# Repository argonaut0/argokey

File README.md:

# Unnamed Keyboard Project

A Custom 65% Mechanical Keyboard with RGB lighting, an OLED status screen, and volume knob.

Possibly with the first ever keyboard firmware fulling supporting multithreading?

### References

- https://datasheets.raspberrypi.com/rp2040/rp2040-datasheet.pdf
- https://datasheets.raspberrypi.com/rp2040/hardware-design-with-rp2040.pdf

### Symbols and Models
- https://github.com/daprice/keyswitches.pretty
- https://app.ultralibrarian.com/details/718f6c74-6ffb-11eb-9033-0a34d6323d74/Raspberry-Pi/RP2040
- https://app.ultralibrarian.com/details/76A34700-1D87-11E9-AB3A-0A3560A4CCCC/Winbond/W25Q64JVSSIQ

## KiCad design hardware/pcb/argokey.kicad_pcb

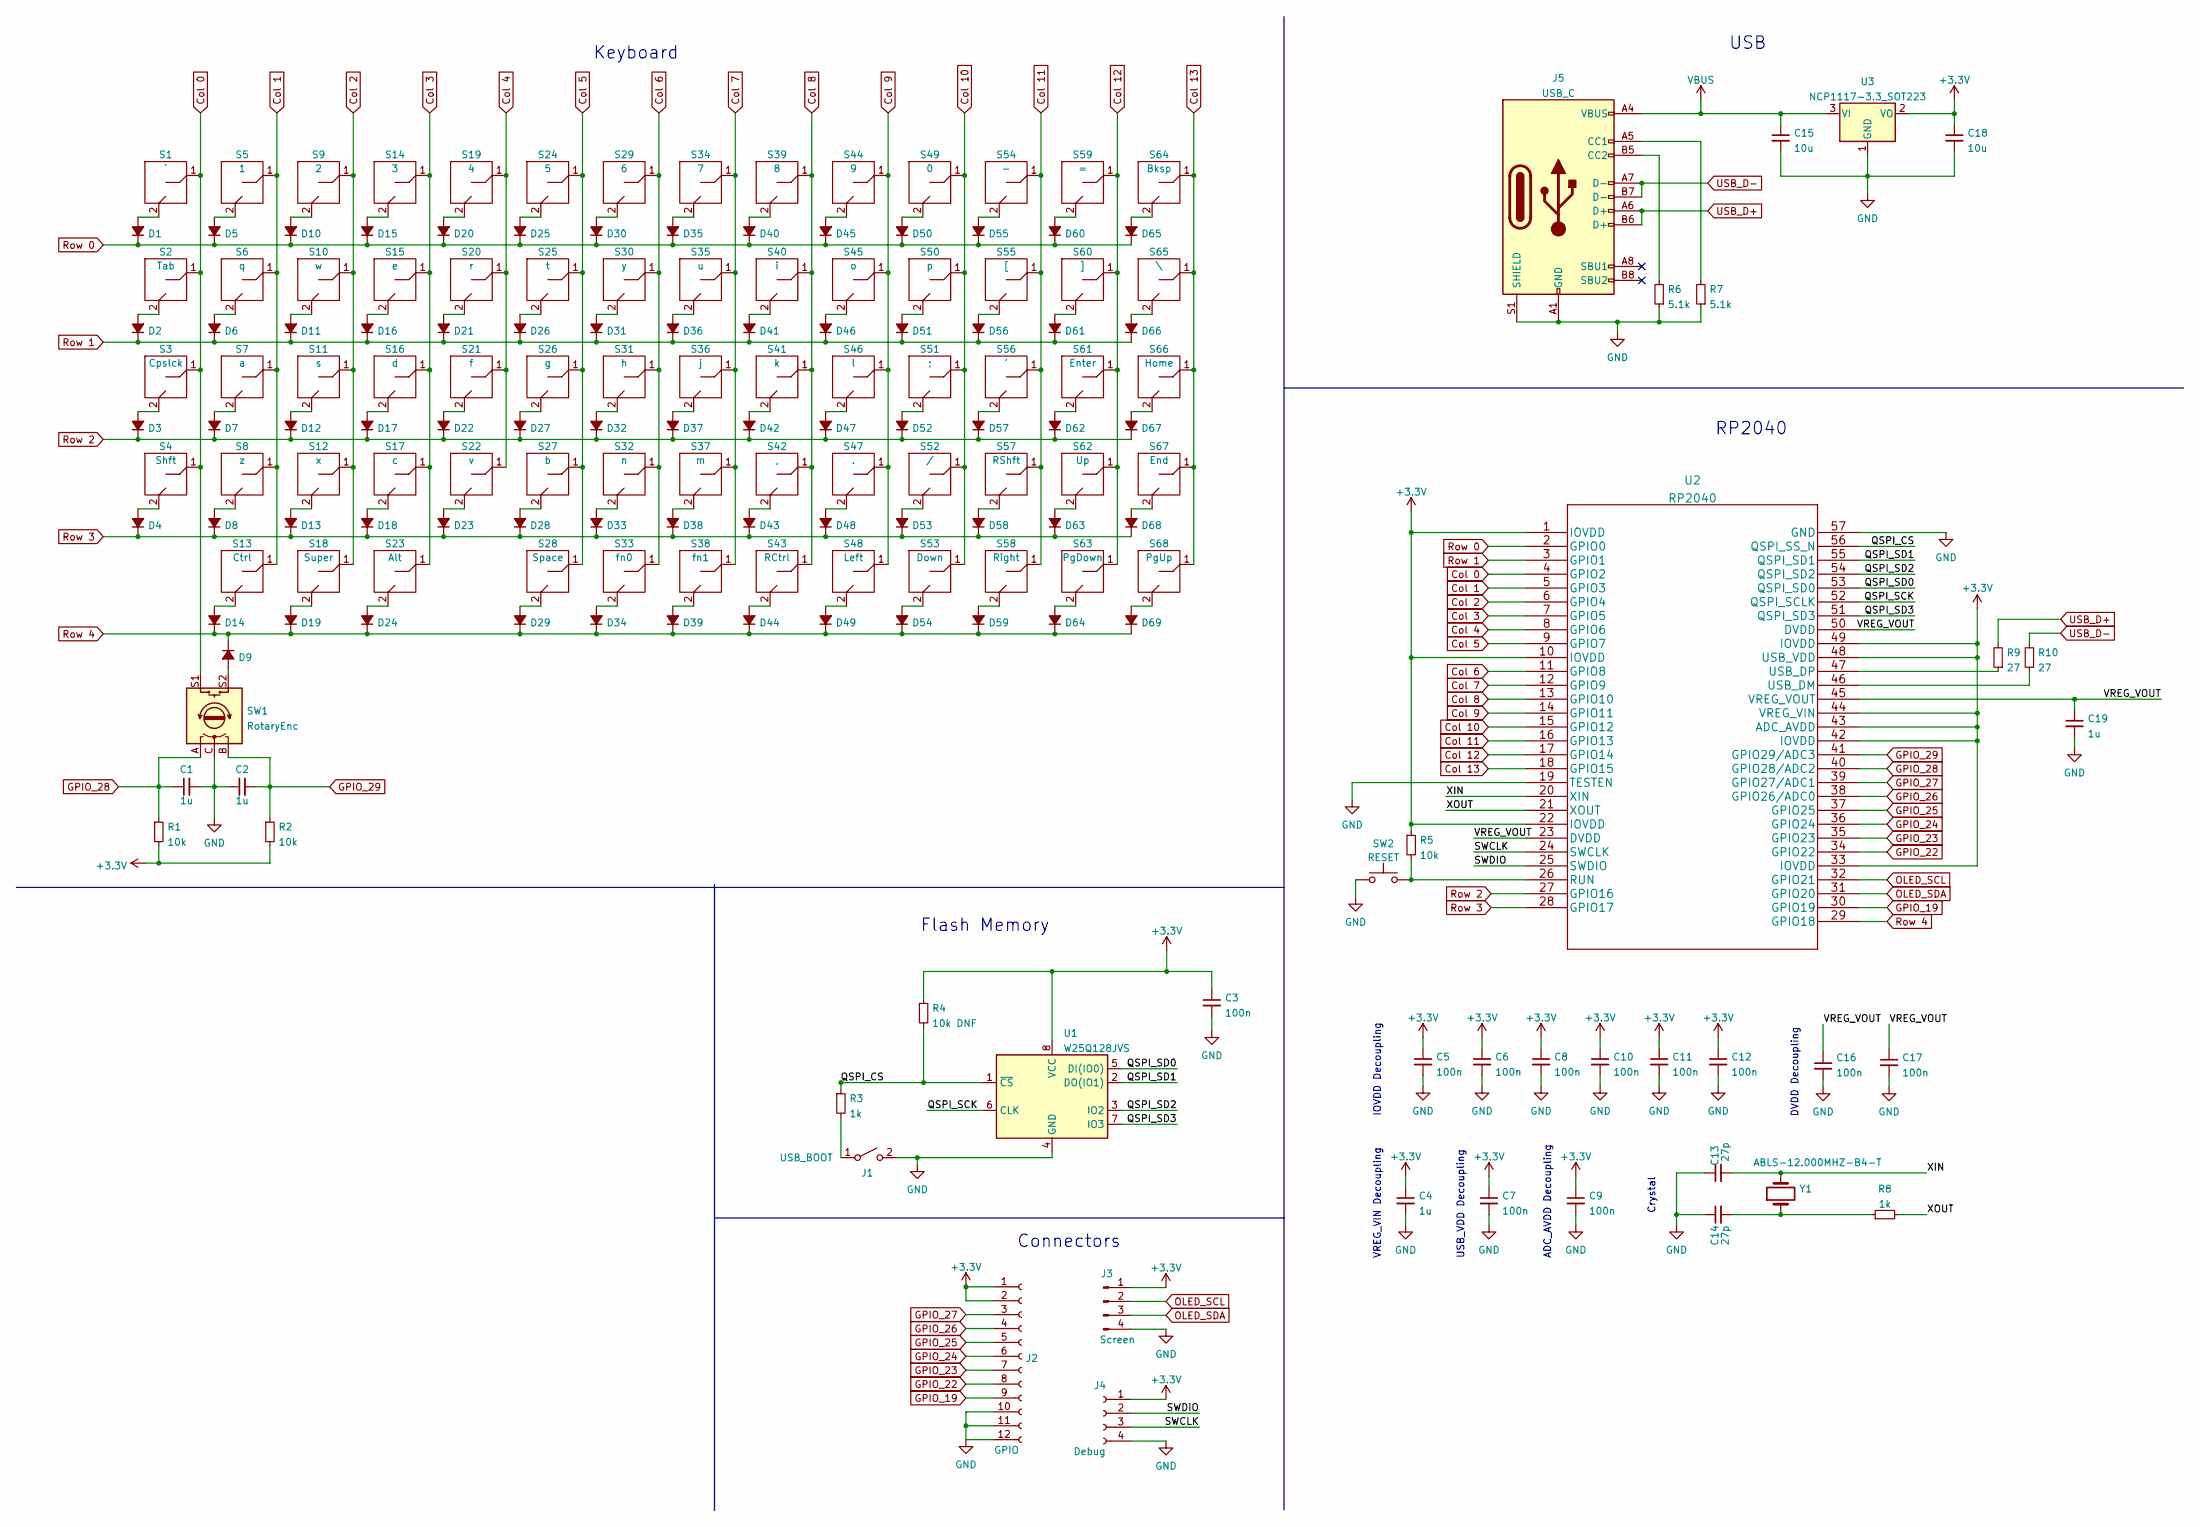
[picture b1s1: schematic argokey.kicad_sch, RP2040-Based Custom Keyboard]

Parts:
C1, C2, C4, C19: 1u; C_0402_1005Metric_Pad0.74x0.62mm_HandSolder
C3, C5, C6, C7, C8, C9, C10, C11, C12, C16, C17: 100n; C_0402_1005Metric_Pad0.74x0.62mm_HandSolder
C13, C14: 27p; C_0402_1005Metric_Pad0.74x0.62mm_HandSolder
C15, C18: 10u; C_0805_2012Metric_Pad1.18x1.45mm_HandSolder
D1, D2, D3, D4, D5, D6, D7, D8, D9, D10, D11, D12, D13, D14, D15, D16, D18, D19, D20, D21, D22, D23, D24, D25, D26, D27, D28, D29, D30, D31, D32, D33, D34, D35, D36, D37, D38, D39, D40, D41, D42, D43, D44, D45, D46, D47, D48, D49, D50, D51, D52, D53, D54, D55, D56, D57, D58, D59, D60, D61, D62, D63, D64, D65, D66, D67, D68, D69: D_SOD-123
D17: D_SOD-123
J1: USB_BOOT; SW_SPDT_PCM12
J2: GPIO; PinSocket_1x12_P2.54mm_Horizontal
J3: Screen; PinHeader_1x04_P2.54mm_Vertical
J4: Debug; PinSocket_1x04_P2.54mm_Horizontal
J5: USB_C; USB_C_Receptacle_GCT_USB4085
R1, R2, R5: 10k; R_0402_1005Metric_Pad0.72x0.64mm_HandSolder
R3, R8: 1k; R_0402_1005Metric_Pad0.72x0.64mm_HandSolder
R4: 10k DNF; R_0402_1005Metric_Pad0.72x0.64mm_HandSolder
R6, R7: 5.1k; R_0402_1005Metric_Pad0.72x0.64mm_HandSolder
R9, R10: 27; R_0402_1005Metric_Pad0.72x0.64mm_HandSolder
S1: `; SW_Cherry_MX_1.00u_PCB
S2: Tab; SW_Cherry_MX_1.50u_PCB
S3: Cpslck; SW_Cherry_MX_1.75u_PCB
S4: Shft; SW_Cherry_MX_2.25u_PCB
S5: 1; SW_Cherry_MX_1.00u_PCB
S6: q; SW_Cherry_MX_1.00u_PCB
S7: a; SW_Cherry_MX_1.00u_PCB
S8: z; SW_Cherry_MX_1.00u_PCB
S9: 2; SW_Cherry_MX_1.00u_PCB
S10: w; SW_Cherry_MX_1.00u_PCB
S11: s; SW_Cherry_MX_1.00u_PCB
S12: x; SW_Cherry_MX_1.00u_PCB
S13: Ctrl; SW_Cherry_MX_1.25u_PCB
S14: 3; SW_Cherry_MX_1.00u_PCB
S15: e; SW_Cherry_MX_1.00u_PCB
S16: d; SW_Cherry_MX_1.00u_PCB
S17: c; SW_Cherry_MX_1.00u_PCB
S18: Super; SW_Cherry_MX_1.25u_PCB
S19: 4; SW_Cherry_MX_1.00u_PCB
S20: r; SW_Cherry_MX_1.00u_PCB
S21: f; SW_Cherry_MX_1.00u_PCB
S22: v; SW_Cherry_MX_1.00u_PCB
S23: Alt; SW_Cherry_MX_1.25u_PCB
S24: 5; SW_Cherry_MX_1.00u_PCB
S25: t; SW_Cherry_MX_1.00u_PCB
S26: g; SW_Cherry_MX_1.00u_PCB
S27: b; SW_Cherry_MX_1.00u_PCB
S28: Space; SW_Cherry_MX_6.25u_PCB
S29: 6; SW_Cherry_MX_1.00u_PCB
S30: y; SW_Cherry_MX_1.00u_PCB
S31: h; SW_Cherry_MX_1.00u_PCB
S32: n; SW_Cherry_MX_1.00u_PCB
S33: fn0; SW_Cherry_MX_1.00u_PCB
S34: 7; SW_Cherry_MX_1.00u_PCB
S35: u; SW_Cherry_MX_1.00u_PCB
S36: j; SW_Cherry_MX_1.00u_PCB
S37: m; SW_Cherry_MX_1.00u_PCB
S38: fn1; SW_Cherry_MX_1.00u_PCB
S39: 8; SW_Cherry_MX_1.00u_PCB
S40: i; SW_Cherry_MX_1.00u_PCB
S41: k; SW_Cherry_MX_1.00u_PCB
S42: ,; SW_Cherry_MX_1.00u_PCB
S43: RCtrl; SW_Cherry_MX_1.00u_PCB
S44: 9; SW_Cherry_MX_1.00u_PCB
S45: o; SW_Cherry_MX_1.00u_PCB
S46: l; SW_Cherry_MX_1.00u_PCB
S47: .; SW_Cherry_MX_1.00u_PCB
S48: Left; SW_Cherry_MX_1.00u_PCB
S49: 0; SW_Cherry_MX_1.00u_PCB
S50: p; SW_Cherry_MX_1.00u_PCB
S51: ;; SW_Cherry_MX_1.00u_PCB
S52: /; SW_Cherry_MX_1.00u_PCB
S53: Down; SW_Cherry_MX_1.00u_PCB
S54: -; SW_Cherry_MX_1.00u_PCB
S55: [; SW_Cherry_MX_1.00u_PCB
S56: '; SW_Cherry_MX_1.00u_PCB
S57: RShft; SW_Cherry_MX_1.75u_PCB
S58: Right; SW_Cherry_MX_1.00u_PCB
S59: =; SW_Cherry_MX_1.00u_PCB
S60: ]; SW_Cherry_MX_1.00u_PCB
S61: Enter; SW_Cherry_MX_2.25u_PCB
S62: Up; SW_Cherry_MX_1.00u_PCB
S63: PgDown; SW_Cherry_MX_1.00u_PCB
S64: Bksp; SW_Cherry_MX_2.00u_PCB
S65: \; SW_Cherry_MX_1.50u_PCB
S66: Home; SW_Cherry_MX_1.00u_PCB
S67: End; SW_Cherry_MX_1.00u_PCB
S68: PgUp; SW_Cherry_MX_1.00u_PCB
SW1: RotaryEnc; RotaryEncoder_Alps_EC12E-Switch_Vertical_H20mm
SW2: RESET; SW_Tactile_SPST_Angled_PTS645Vx83-2LFS
U1: W25Q128JVS; SOIC-8_5.23x5.23mm_P1.27mm
U2: RP2040; RP2040-QFN-56
U3: NCP1117-3.3_SOT223; SOT-223-3_TabPin2
Y1: ABLS-12.000MHZ-B4-T; Crystal_SMD_HC49-US

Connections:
+3V3: C3.1, C4.1, C5.1, C6.1, C7.1, C8.1, C9.1, C10.1, C11.1, C12.1, C18.1, J2.1, J2.2, J3.1, J4.1, R1.2, R2.2, R4.1, R5.1, U1.8 (VCC), U2.1 (IOVDD), U2.10 (IOVDD), U2.22 (IOVDD), U2.33 (IOVDD), U2.42 (IOVDD), U2.43 (ADC_AVDD), U2.44 (VREG_VIN), U2.48 (USB_VDD), U2.49 (IOVDD), U3.2 (VO)
/QSPI_CS: R3.1, R4.2, U1.1 (~CS), U2.56 (QSPI_SS_N)
/QSPI_SCK: U1.6 (CLK), U2.52 (QSPI_SCLK)
/QSPI_SD0: U1.5 (DI(IO0)), U2.53 (QSPI_SD0)
/QSPI_SD1: U1.2 (DO(IO1)), U2.55 (QSPI_SD1)
/QSPI_SD2: U1.3 (IO2), U2.54 (QSPI_SD2)
/QSPI_SD3: U1.7 (IO3), U2.51 (QSPI_SD3)
/SWCLK: J4.3, U2.24 (SWCLK)
/SWDIO: J4.2, U2.25 (SWDIO)
/VREG_VOUT: C16.1, C17.1, C19.1, U2.23 (DVDD), U2.45 (VREG_VOUT), U2.50 (DVDD)
/XIN: C13.2, U2.20 (XIN), Y1.2
/XOUT: R8.2, U2.21 (XOUT)
Col 0: S1.1, S2.1, S3.1, S4.1, SW1.S1, U2.4 (GPIO2)
Col 1: S5.1, S6.1, S7.1, S8.1, S13.1, U2.5 (GPIO3)
Col 2: S9.1, S10.1, S11.1, S12.1, S18.1, U2.6 (GPIO4)
Col 3: S14.1, S15.1, S16.1, S17.1, S23.1, U2.7 (GPIO5)
Col 4: S19.1, S20.1, S21.1, S22.1, U2.8 (GPIO6)
Col 5: S24.1, S25.1, S26.1, S27.1, S28.1, U2.9 (GPIO7)
Col 6: S29.1, S30.1, S31.1, S32.1, S33.1, U2.11 (GPIO8)
Col 7: S34.1, S35.1, S36.1, S37.1, S38.1, U2.12 (GPIO9)
Col 8: S39.1, S40.1, S41.1, S42.1, S43.1, U2.13 (GPIO10)
Col 9: S44.1, S45.1, S46.1, S47.1, S48.1, U2.14 (GPIO11)
Col 10: S49.1, S50.1, S51.1, S52.1, S53.1, U2.15 (GPIO12)
Col 11: S54.1, S55.1, S56.1, S57.1, S58.1, U2.16 (GPIO13)
Col 12: S59.1, S60.1, S61.1, S62.1, S63.1, U2.17 (GPIO14)
Col 13: S64.1, S65.1, S66.1, S67.1, S68.1, U2.18 (GPIO15)
GND: C1.2, C2.1, C3.2, C4.2, C5.2, C6.2, C7.2, C8.2, C9.2, C10.2, C11.2, C12.2, C13.1, C14.1, C15.2, C16.2, C17.2, C18.2, C19.2, J1.2 (B), J2.10, J2.11, J2.12, J3.4, J4.4, J5.A1 (GND), J5.A12 (GND), J5.B1 (GND), J5.B12 (GND), J5.S1 (SHIELD), R6.1, R7.1, SW1.C, SW2.1, U1.4 (GND), U2.19 (TESTEN), U2.57 (GND), U3.1 (GND)
GPIO_19: J2.9, U2.30 (GPIO19)
GPIO_22: J2.8, U2.34 (GPIO22)
GPIO_23: J2.7, U2.35 (GPIO23)
GPIO_24: J2.6, U2.36 (GPIO24)
GPIO_25: J2.5, U2.37 (GPIO25)
GPIO_26: J2.4, U2.38 (GPIO26/ADC0)
GPIO_27: J2.3, U2.39 (GPIO27/ADC1)
GPIO_28: C1.1, R1.1, SW1.A, U2.40 (GPIO28/ADC2)
GPIO_29: C2.2, R2.1, SW1.B, U2.41 (GPIO29/ADC3)
unnamed: C14.2, R8.1, Y1.1
unnamed: D1.2 (A), S1.2
unnamed: D2.2 (A), S2.2
unnamed: D3.2 (A), S3.2
unnamed: D4.2 (A), S4.2
unnamed: D5.2 (A), S5.2
unnamed: D6.2 (A), S6.2
unnamed: D7.2 (A), S7.2
unnamed: D8.2 (A), S8.2
unnamed: D9.2 (A), SW1.S2
unnamed: D10.2 (A), S9.2
unnamed: D11.2 (A), S10.2
unnamed: D12.2 (A), S11.2
unnamed: D13.2 (A), S12.2
unnamed: D14.2 (A), S13.2
unnamed: D15.2 (A), S14.2
unnamed: D16.2 (A), S15.2
unnamed: D17.2 (A), S16.2
unnamed: D18.2 (A), S17.2
unnamed: D19.2 (A), S18.2
unnamed: D20.2 (A), S19.2
unnamed: D21.2 (A), S20.2
unnamed: D22.2 (A), S21.2
unnamed: D23.2 (A), S22.2
unnamed: D24.2 (A), S23.2
unnamed: D25.2 (A), S24.2
unnamed: D26.2 (A), S25.2
unnamed: D27.2 (A), S26.2
unnamed: D28.2 (A), S27.2
unnamed: D29.2 (A), S28.2
unnamed: D30.2 (A), S29.2
unnamed: D31.2 (A), S30.2
unnamed: D32.2 (A), S31.2
unnamed: D33.2 (A), S32.2
unnamed: D34.2 (A), S33.2
unnamed: D35.2 (A), S34.2
unnamed: D36.2 (A), S35.2
unnamed: D37.2 (A), S36.2
unnamed: D38.2 (A), S37.2
unnamed: D39.2 (A), S38.2
unnamed: D40.2 (A), S39.2
unnamed: D41.2 (A), S40.2
unnamed: D42.2 (A), S41.2
unnamed: D43.2 (A), S42.2
unnamed: D44.2 (A), S43.2
unnamed: D45.2 (A), S44.2
unnamed: D46.2 (A), S45.2
unnamed: D47.2 (A), S46.2
unnamed: D48.2 (A), S47.2
unnamed: D49.2 (A), S48.2
unnamed: D50.2 (A), S49.2
unnamed: D51.2 (A), S50.2
unnamed: D52.2 (A), S51.2
unnamed: D53.2 (A), S52.2
unnamed: D54.2 (A), S53.2
unnamed: D55.2 (A), S54.2
unnamed: D56.2 (A), S55.2
unnamed: D57.2 (A), S56.2
unnamed: D58.2 (A), S57.2
unnamed: D59.2 (A), S58.2
unnamed: D60.2 (A), S59.2
unnamed: D61.2 (A), S60.2
unnamed: D62.2 (A), S61.2
unnamed: D63.2 (A), S62.2
unnamed: D64.2 (A), S63.2
unnamed: D65.2 (A), S64.2
unnamed: D66.2 (A), S65.2
unnamed: D67.2 (A), S66.2
unnamed: D68.2 (A), S67.2
unnamed: D69.2 (A), S68.2
unnamed: J1.1 (A), R3.2
unnamed: J5.A5 (CC1), R7.2
unnamed: J5.B5 (CC2), R6.2
unnamed: R5.2, SW2.2, U2.26 (RUN)
unnamed: R9.1, U2.47 (USB_DP)
unnamed: R10.1, U2.46 (USB_DM)
OLED_SCL: J3.2, U2.32 (GPIO21)
OLED_SDA: J3.3, U2.31 (GPIO20)
Row 0: D1.1 (K), D5.1 (K), D10.1 (K), D15.1 (K), D20.1 (K), D25.1 (K), D30.1 (K), D35.1 (K), D40.1 (K), D45.1 (K), D50.1 (K), D55.1 (K), D60.1 (K), D65.1 (K), U2.2 (GPIO0)
Row 1: D2.1 (K), D6.1 (K), D11.1 (K), D16.1 (K), D21.1 (K), D26.1 (K), D31.1 (K), D36.1 (K), D41.1 (K), D46.1 (K), D51.1 (K), D56.1 (K), D61.1 (K), D66.1 (K), U2.3 (GPIO1)
Row 2: D3.1 (K), D7.1 (K), D12.1 (K), D17.1 (K), D22.1 (K), D27.1 (K), D32.1 (K), D37.1 (K), D42.1 (K), D47.1 (K), D52.1 (K), D57.1 (K), D62.1 (K), D67.1 (K), U2.27 (GPIO16)
Row 3: D4.1 (K), D8.1 (K), D13.1 (K), D18.1 (K), D23.1 (K), D28.1 (K), D33.1 (K), D38.1 (K), D43.1 (K), D48.1 (K), D53.1 (K), D58.1 (K), D63.1 (K), D68.1 (K), U2.28 (GPIO17)
Row 4: D9.1 (K), D14.1 (K), D19.1 (K), D24.1 (K), D29.1 (K), D34.1 (K), D39.1 (K), D44.1 (K), D49.1 (K), D54.1 (K), D59.1 (K), D64.1 (K), D69.1 (K), U2.29 (GPIO18)
USB_D+: J5.A6 (D+), J5.B6 (D+), R9.2
USB_D-: J5.A7 (D-), J5.B7 (D-), R10.2
VBUS: C15.1, J5.A4 (VBUS), J5.A9 (VBUS), J5.B4 (VBUS), J5.B9 (VBUS), U3.3 (VI); also elsewhere on the board

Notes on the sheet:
Keyboard
Flash Memory
USB
Connectors
USB_VDD Decoupling
RP2040
ADC_AVDD Decoupling
IOVDD Decoupling
DVDD Decoupling
VREG_VIN Decoupling
Crystal

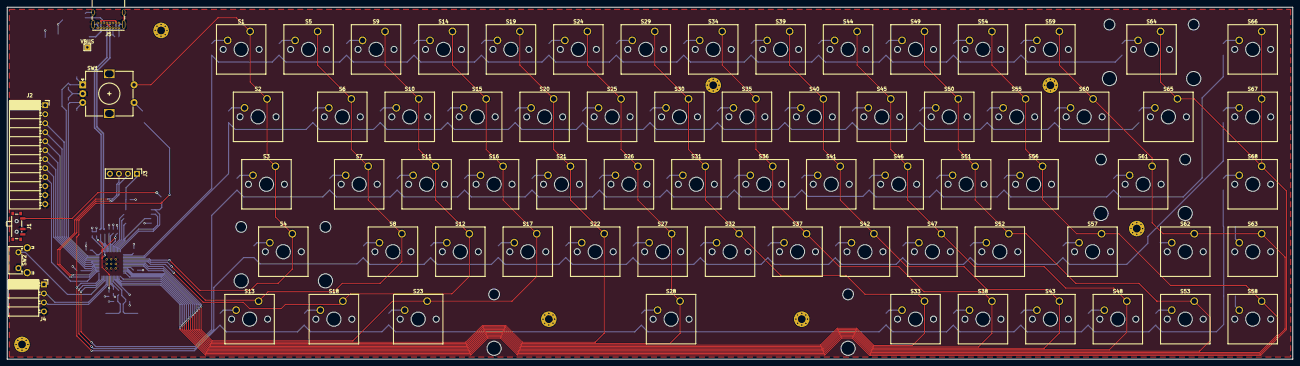
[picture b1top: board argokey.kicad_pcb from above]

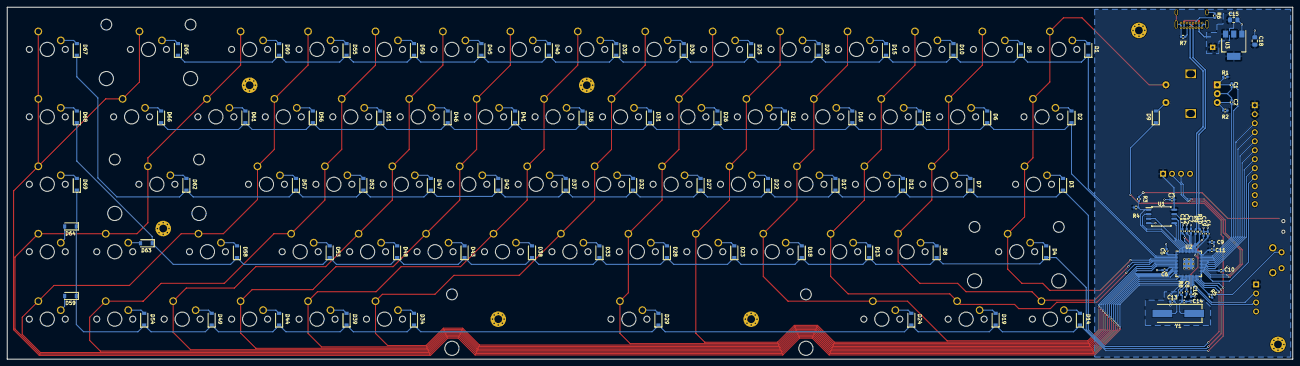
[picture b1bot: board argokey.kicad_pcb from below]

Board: 2 copper layers, 363.1 x 99.4 mm, 178 parts (102 on the bottom side), 122 nets.

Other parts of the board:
VBUS: TestPoint_THTPad_1.5x1.5mm_Drill0.7mm

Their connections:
VBUS: VBUS.1; also elsewhere on the board

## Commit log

2022-01-04 Add README
2022-01-05 Remove gitignore files
2022-01-05 Change flash to 16M
2022-01-05 Schematic: RP2040 Power
2022-01-05 Rev 1 Schematic
2022-01-06 Sch: Add connectors
2022-01-06 Sch: Replace Flash, Mark Non-con
2022-01-06 Sch: Set USB GND VBUS power output
2022-01-06 Sch: Update RP2040 symbol pin types
2022-01-06 "Sch: Assign most footprints"
2022-01-06 Clean libs, update RP2040 sym lib
2022-01-06 Sch: Remove Diode values
2022-01-06 PCB: Layout keys/diodes
2022-01-07 PCB: Most traces
2022-01-08 PCB: All
2022-01-10 PCB: Fix Errors
2022-04-18 Meta filesx
2022-04-18 Move all smd on one side
2022-04-18 Rev 2 Draft
2022-04-22 Cleanup
2022-06-07 First prod rev
